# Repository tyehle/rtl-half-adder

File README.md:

# RTL Half Adder Circuit

A half adder circuit implemented with resistor transistor logic. All essential logic is on the front with through hole parts, and additional lights are surface mount on the back.

# Schematic

# BOM

| Reference                                                                                   | Value        | Part Number       | Quantity | Datasheet                                                                                                  | Link                                                                    |
|---------------------------------------------------------------------------------------------|--------------|-------------------|----------|------------------------------------------------------------------------------------------------------------|-------------------------------------------------------------------------|
| BT1                                                                                         | Battery_Cell | BAT-HLD-012-THM   | 1        | [Datasheet](https://linxtechnologies.com/wp/wp-content/uploads/bat-hld-012-thm.pdf)                        | [mouser.com](https://www.mouser.com/ProductDetail/BAT-HLD-012-THM)      |
| D1 D2                                                                                       | Red          | LTL-4223          | 2        | [Datasheet](https://optoelectronics.liteon.com/upload/download/DS20-2003-313/LTL-4223-032A.pdf)            | [mouser.com](https://www.mouser.com/ProductDetail/LTL-4223)             |
| D3 D4                                                                                       | Green        | LTL-4233          | 2        | [Datasheet](https://optoelectronics.liteon.com/upload/download/DS-20-92-1097/4233DG.pdf)                   | [mouser.com](https://www.mouser.com/ProductDetail/LTL-4233)             |
| D10 D11 D12 D13 D14 D15 D16 D17 D18 D19 D20 D21 D22 D23 D24 D25 D26 D27 D5 D6 D7 D8 D9      | Yellow       | LTST-C230KSKT     | 23       | [Datasheet](https://optoelectronics.liteon.com/upload/download/DS22-2000-254/LTST-C230KSKT.pdf)            | [mouser.com](https://www.mouser.com/ProductDetail/859-LTST-C230KSKT)    |
| Q16 Q17 Q18 Q19                                                                             | Q_NPN_BEC    | MMBT3904,215      | 4        | [Datasheet](https://assets.nexperia.com/documents/data-sheet/MMBT3904.pdf)                                 | [mouser.com](https://www.mouser.com/ProductDetail/MMBT3904215)          |
| Q1 Q10 Q11 Q12 Q13 Q14 Q15 Q2 Q3 Q4 Q5 Q6 Q7 Q8 Q9                                          | Q_NPN_EBC    | 2N3904BU          | 15       | [Datasheet](https://www.onsemi.com/pub/Collateral/2N3904-D.pdf)                                            | [mouser.com](https://www.mouser.com/ProductDetail/2N3904BU)             |
| R2 R26 R27 R4                                                                               | 510          | CFR-25JR-52-510R  | 4        | [Datasheet](http://www.yageo.com/NewPortal/yageodocoutput?fileName=/pdf/throughhole/Yageo_LR_CFR_2013.pdf) | [mouser.com](https://www.mouser.com/ProductDetail/CFR-25JR-52-510R)     |
| R28 R31 R35 R38                                                                             | 10k          | CR0805-FX-1002ELF | 4        | [Datasheet](https://www.bourns.com/pdfs/chpreztr.pdf)                                                      | [mouser.com](https://www.mouser.com/ProductDetail/652-CR0805FX-1002ELF) |
| R29 R30 R32 R33 R34 R36 R37 R39 R40 R41 R42 R43 R44 R45 R46 R47 R48 R49 R50 R51 R52 R53 R54 | 510          | CR0805-FX-5100ELF | 23       | [Datasheet](https://www.bourns.com/pdfs/chpreztr.pdf)                                                      | [mouser.com](https://www.mouser.com/ProductDetail/652-CR0805FX-5100ELF) |
| R1 R10 R11 R13 R14 R15 R16 R19 R21 R22 R24 R25 R3 R5 R6 R7 R8                               | 10k          | CFR-25JT-52-10K   | 17       | [Datasheet](http://www.yageo.com/NewPortal/yageodocoutput?fileName=/pdf/throughhole/Yageo_LR_CFR_2013.pdf) | [mouser.com](https://www.mouser.com/ProductDetail/CFR-25JT-52-10K)      |
| R12 R17 R18 R20 R23 R9                                                                      | 1k           | CFR-25JT-52-1K    | 6        | [Datasheet](http://www.yageo.com/NewPortal/yageodocoutput?fileName=/pdf/throughhole/Yageo_LR_CFR_2013.pdf) | [mouser.com](https://www.mouser.com/ProductDetail/CFR-25JT-52-1K)       |
| SW1 SW2 SW3                                                                                 | SW_SPDT      | EG1218            | 3        | [Datasheet](https://www.e-switch.com/system/asset/product_line/data_sheet/119/EG.pdf)                      | [mouser.com](https://www.mouser.com/ProductDetail/EG1218)               |

# Assembly notes
[PDF](docs/rtl-half-adder-assembly.pdf)

# LICENSE

This work is licensed under a [Creative Commons Attribution-NonCommercial-ShareAlike 4.0 International License](http://creativecommons.org/licenses/by-nc-sa/4.0/).

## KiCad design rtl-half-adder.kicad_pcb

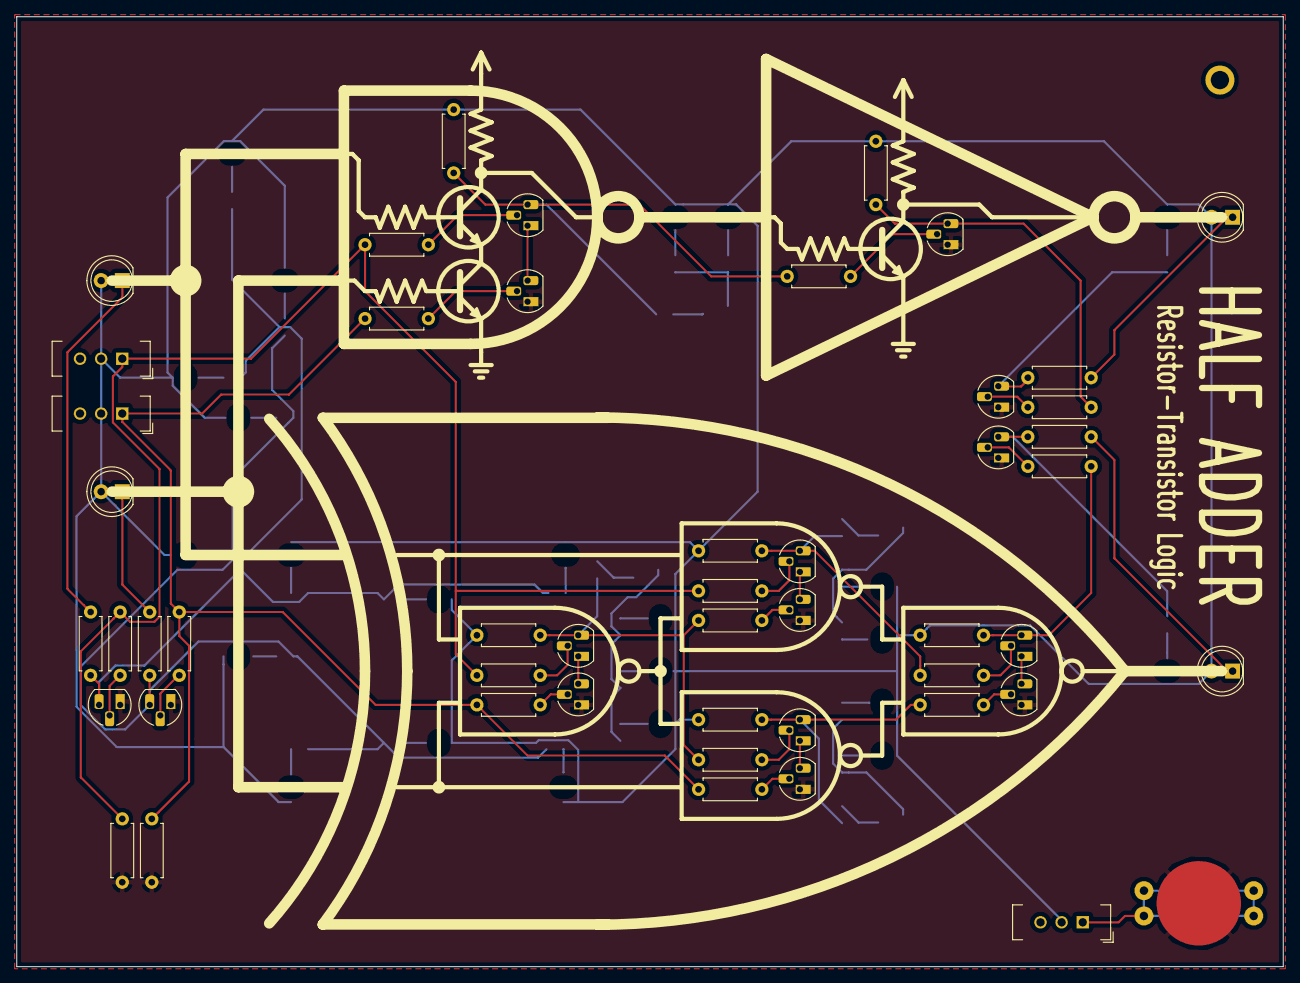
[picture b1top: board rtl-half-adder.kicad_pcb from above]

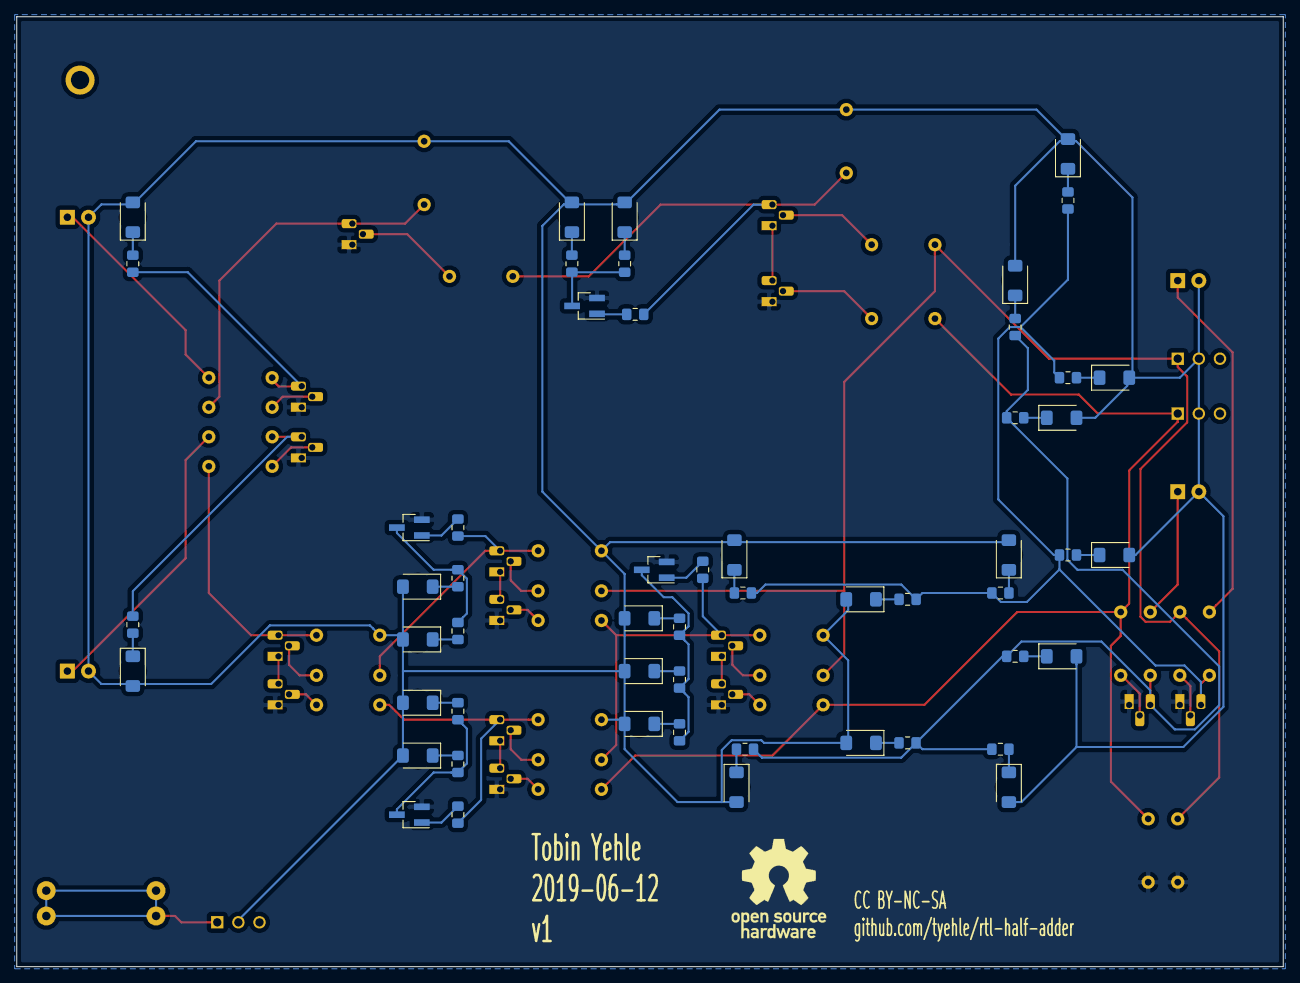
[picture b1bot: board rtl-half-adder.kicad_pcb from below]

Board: 2 copper layers, 152.4 x 114.3 mm, 104 parts (54 on the bottom side), 70 nets.

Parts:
BT1: Battery_Cell; BatteryHolder_CR1220_THT
D1, D2: Red; LED_D5.0mm
D3, D4: Green; LED_D5.0mm
D5, D6, D7, D8, D9, D10, D11, D12, D13, D14, D15, D16, D17, D18, D19, D20, D21, D22, D23, D24, D25, D26, D27: Yellow; LED_1206_ReverseMountSquare1.5mm_HandSolder
Q1, Q2, Q3, Q4, Q5, Q6, Q7, Q8, Q9, Q10, Q11, Q12, Q13, Q14, Q15: Q_NPN_EBC; TO-92_HandSolder
Q16, Q17, Q18, Q19: Q_NPN_BEC; SOT-23_Handsoldering
R1, R3, R5, R6, R7, R8, R10, R11, R13, R14, R15, R16, R19, R21, R22, R24, R25: 10k; R_Axial_DIN0207_L6.3mm_D2.5mm_P7.62mm_Horizontal
R2, R4, R26, R27: 510; R_Axial_DIN0207_L6.3mm_D2.5mm_P7.62mm_Horizontal
R9, R12, R17, R18, R20, R23: 1k; R_Axial_DIN0207_L6.3mm_D2.5mm_P7.62mm_Horizontal
R28, R31, R35, R38: 10k; R_0805_2012Metric_Pad1.15x1.40mm_HandSolder
R29, R30, R32, R33, R34, R36, R37, R39, R40, R41, R42, R43, R44, R45, R46, R47, R48, R49, R50, R51, R52, R53, R54: 510; R_0805_2012Metric_Pad1.15x1.40mm_HandSolder
SW1, SW2, SW3: SW_SPDT; SW_EG1218_SPDT

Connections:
/A_GATE: Q1.3, R2.2, R41.2, R42.2, R43.2, R44.2, R45.2, R46.2
/B_GATE: Q2.3, R4.2, R47.2, R48.2, R49.2, R50.2, R51.2, R52.2
/CARRY_GATE: Q14.3, R26.2, R53.2
/SUM_GATE: Q15.3, R27.2, R54.2
A: R1.2, R6.1, R7.2, R10.2, R13.2, SW2.1
B: R3.2, R5.1, R8.2, R11.2, R16.2, SW3.1
CARRY: Q11.3, R20.2, R24.2
GND: BT1.2, Q1.1, Q2.1, Q4.1, Q6.1, Q8.1, Q10.1, Q11.1, Q13.1, Q14.1, Q15.1, Q16.2, Q17.2, Q18.2, Q19.2, R5.2, R6.2
NAND1: Q5.3, R12.2, R19.2, R28.2
unnamed: BT1.1, SW1.1
unnamed: D1.1, R2.1
unnamed: D2.1, R4.1
unnamed: D3.1, R26.1
unnamed: D4.1, R27.1
unnamed: D5.1, R29.1
unnamed: D6.1, R30.1
unnamed: D7.1, R32.1
unnamed: D8.1, R33.1
unnamed: D9.1, R34.1
unnamed: D10.1, R36.1
unnamed: D11.1, R37.1
unnamed: D12.1, R39.1
unnamed: D13.1, R40.1
unnamed: D14.1, R41.1
unnamed: D15.1, R42.1
unnamed: D16.1, R43.1
unnamed: D17.1, R44.1
unnamed: D18.1, R45.1
unnamed: D19.1, R46.1
unnamed: D20.1, R47.1
unnamed: D21.1, R48.1
unnamed: D22.1, R49.1
unnamed: D23.1, R50.1
unnamed: D24.1, R51.1
unnamed: D25.1, R52.1
unnamed: D26.1, R53.1
unnamed: D27.1, R54.1
unnamed: Q1.2, R1.1
unnamed: Q2.2, R3.1
unnamed: Q3.1, Q4.3
unnamed: Q3.2, R7.1
unnamed: Q4.2, R8.1
unnamed: Q5.1, Q6.3
unnamed: Q5.2, R10.1
unnamed: Q6.2, R11.1
unnamed: Q7.1, Q8.3
unnamed: Q7.2, R13.1
unnamed: Q8.2, R14.1
unnamed: Q9.2, R15.1
unnamed: Q10.2, R16.1
unnamed: Q9.1, Q10.3
unnamed: Q11.2, R19.1
unnamed: Q12.1, Q13.3
unnamed: Q12.2, R21.1
unnamed: Q13.2, R22.1
unnamed: Q14.2, R24.1
unnamed: Q15.2, R25.1
unnamed: Q16.1, R28.1
unnamed: Q16.3, R29.2, R30.2
unnamed: Q17.1, R31.1
unnamed: Q17.3, R32.2, R33.2, R34.2
unnamed: Q18.1, R35.1
unnamed: Q18.3, R36.2, R37.2
unnamed: Q19.1, R38.1
unnamed: Q19.3, R39.2, R40.2
SUM: Q12.3, R23.2, R25.2
VCC: D1.2, D2.2, D3.2, D4.2, D5.2, D6.2, D7.2, D8.2, D9.2, D10.2, D11.2, D12.2, D13.2, D14.2, D15.2, D16.2, D17.2, D18.2, D19.2, D20.2, D21.2, D22.2, D23.2, D24.2, D25.2, D26.2, D27.2, R9.1, R12.1, R17.1, R18.1, R20.1, R23.1, SW1.2, SW2.2, SW3.2
XOR1: Q3.3, R9.2, R14.2, R15.2, R31.2
XOR2: Q7.3, R17.2, R21.2, R35.2
XOR3: Q9.3, R18.2, R22.2, R38.2

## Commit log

2019-06-06 add falstad files
2019-06-06 schematic and xor layout done
2019-06-08 through hole components and silk screen done
2019-06-09 copy an led footprint with a reverse mount hole to a local lib
2019-06-09 update footprints for smd leds
2019-06-09 inter gate led layout done
2019-06-10 add battery footprint
2019-06-10 add link and datasheet for battery clip
2019-06-11 update schematic
2019-06-11 refactor numeric assignments
2019-06-11 fix front fab layer
2019-06-11 put notes on the back
2019-06-12 full smd led array layout done
2019-06-12 layout all done
2019-06-13 fix issues with some tracks
2019-06-14 add sheet annotations
2019-06-14 add schematic svgs
2019-06-14 add gerbers
2019-06-14 add black and white board docs
2019-06-14 add svg board renders
2019-06-14 rename schematic svg
2019-07-31 change led footprint
2019-07-31 regen gerbers
2019-07-31 regen renders
2019-07-31 regen docs
2019-09-04 add updated smd led footprint
2019-09-04 more part links and BOM
2019-09-04 add io led specs
2019-09-08 finish bom
2019-09-18 regen svgs
2019-09-18 regen netlist with updated labels
2019-09-18 update fab layer with new labels
2019-09-18 update doc svgs
2019-09-18 add bom to readme
2019-09-25 add assembly notes

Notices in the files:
rtl-half-adder.kicad_pcb:
CC BY-NC-SA
